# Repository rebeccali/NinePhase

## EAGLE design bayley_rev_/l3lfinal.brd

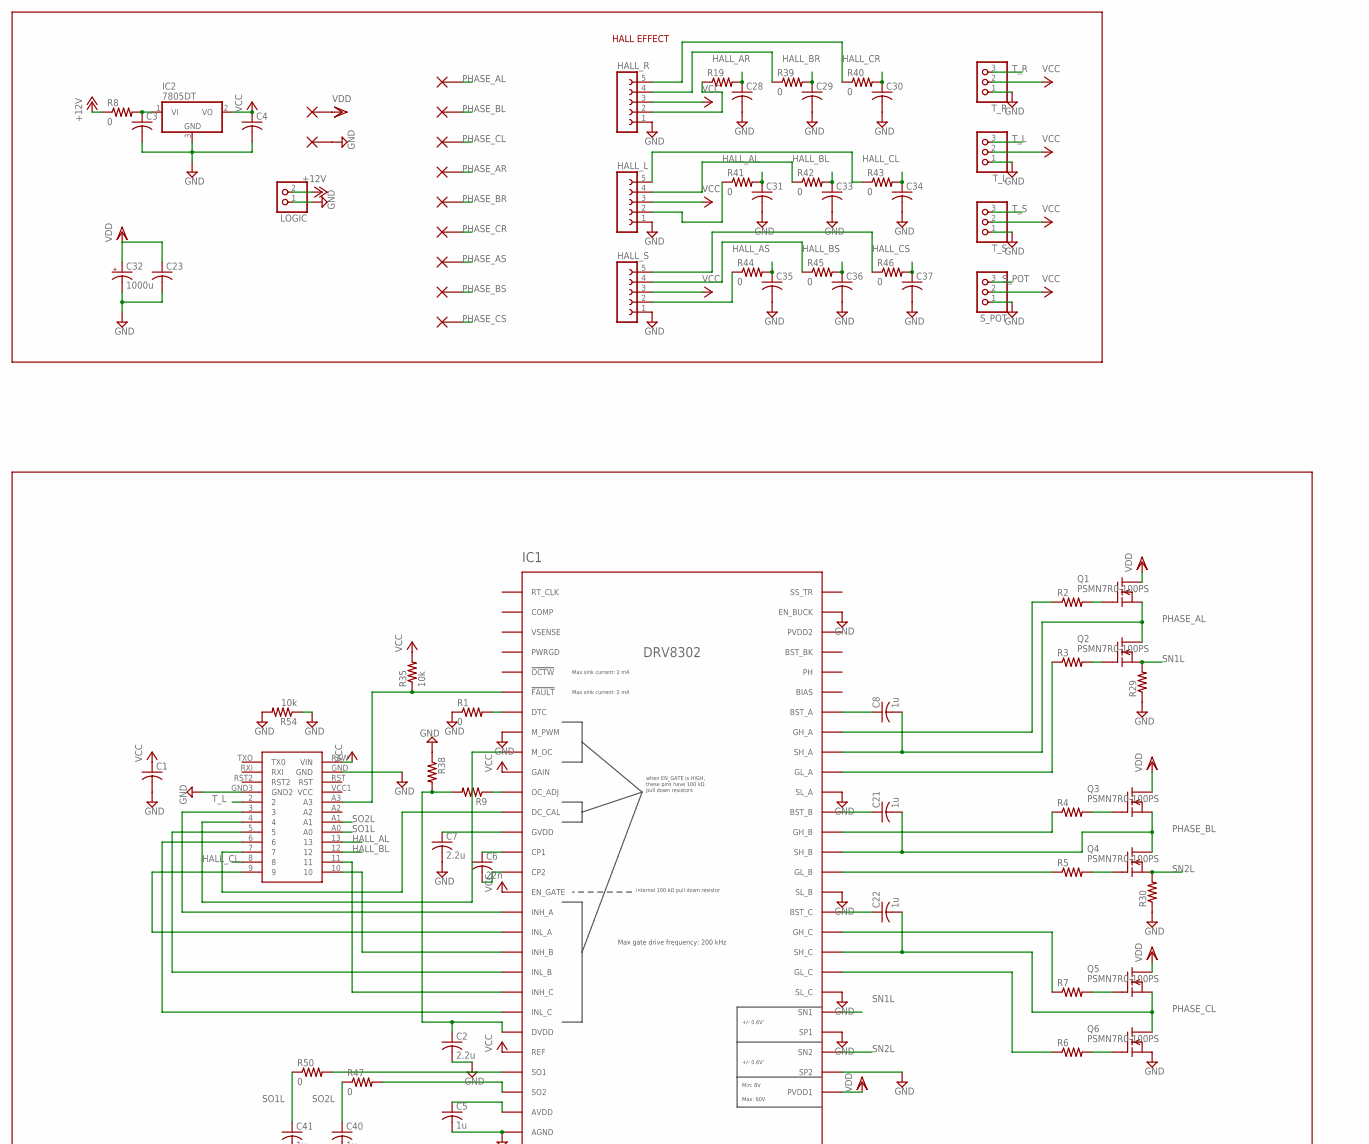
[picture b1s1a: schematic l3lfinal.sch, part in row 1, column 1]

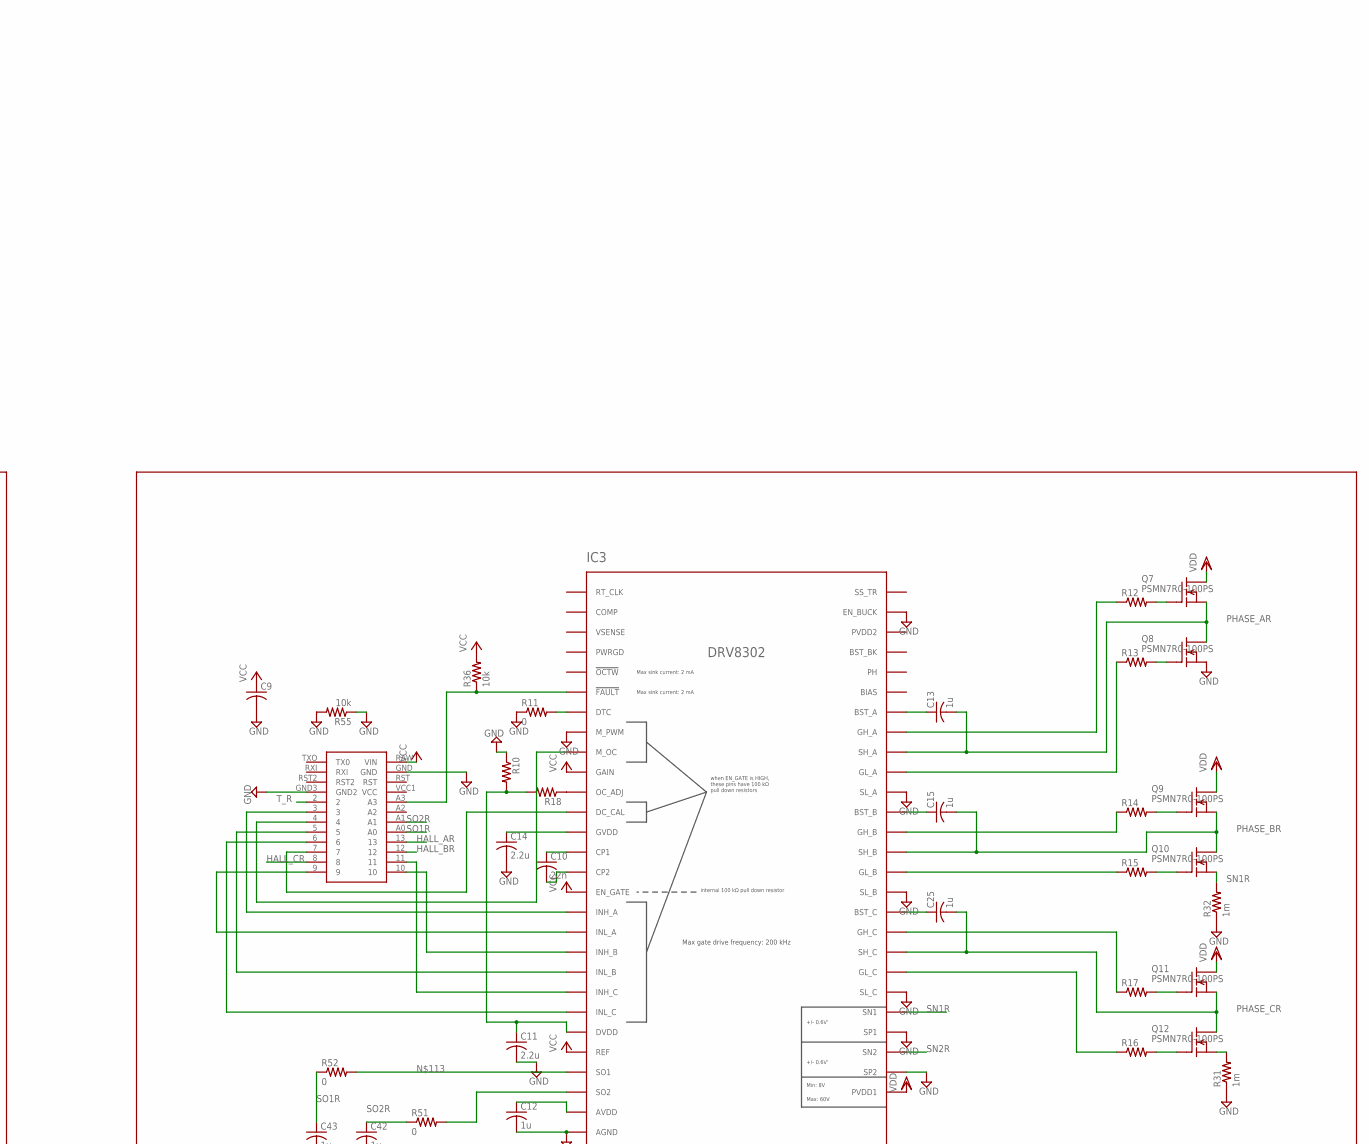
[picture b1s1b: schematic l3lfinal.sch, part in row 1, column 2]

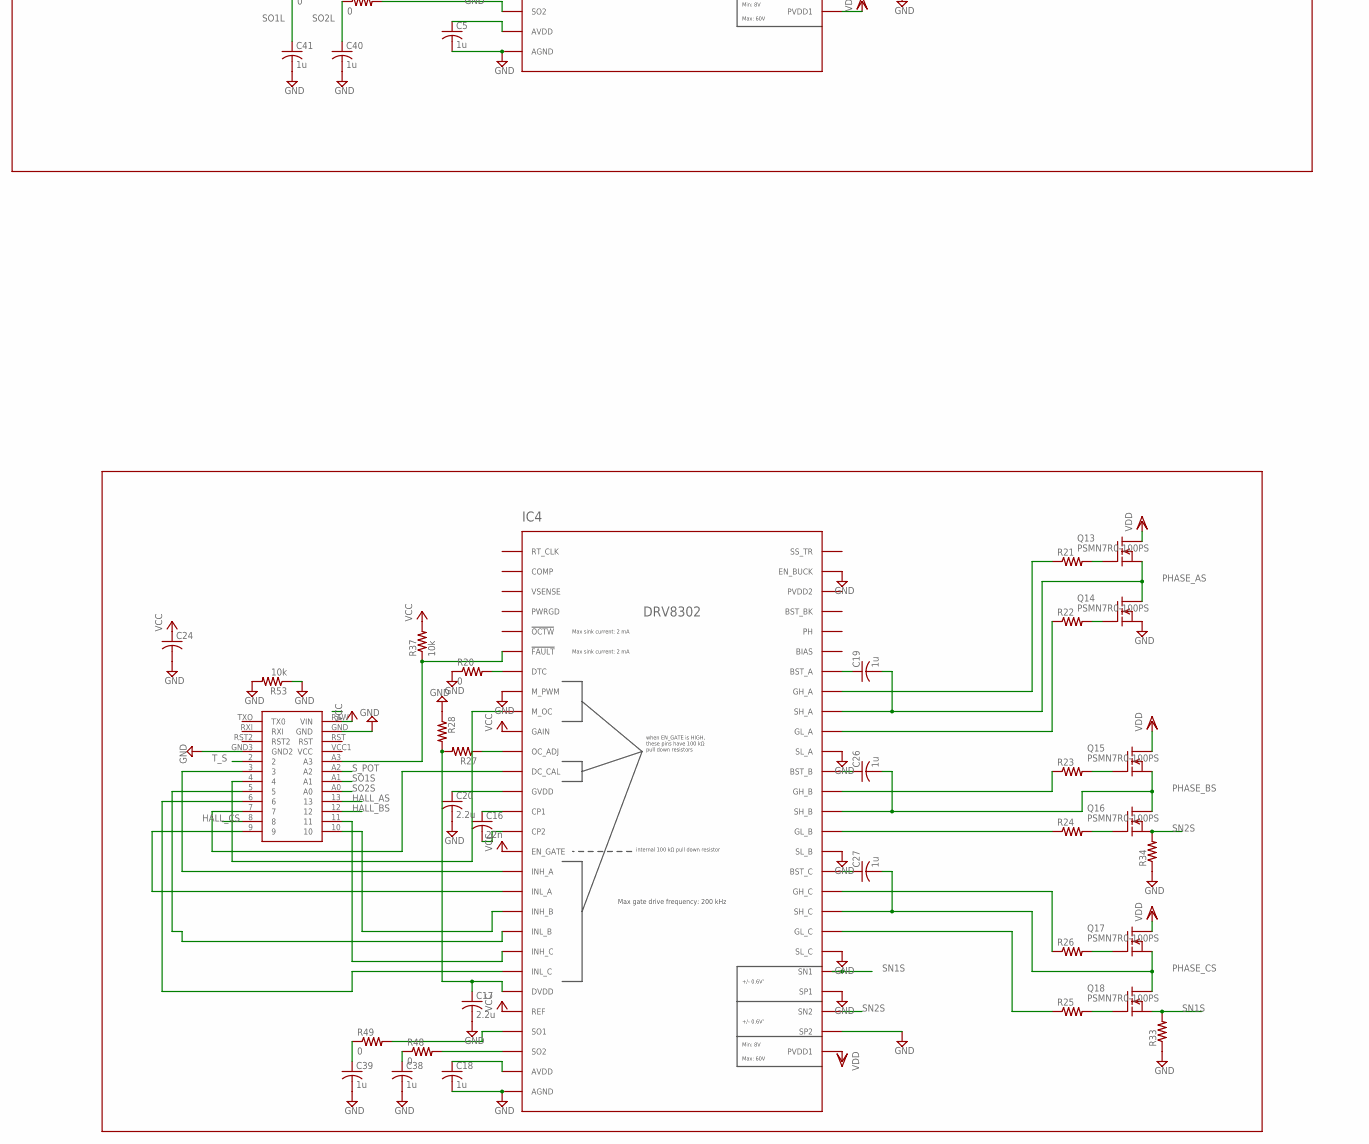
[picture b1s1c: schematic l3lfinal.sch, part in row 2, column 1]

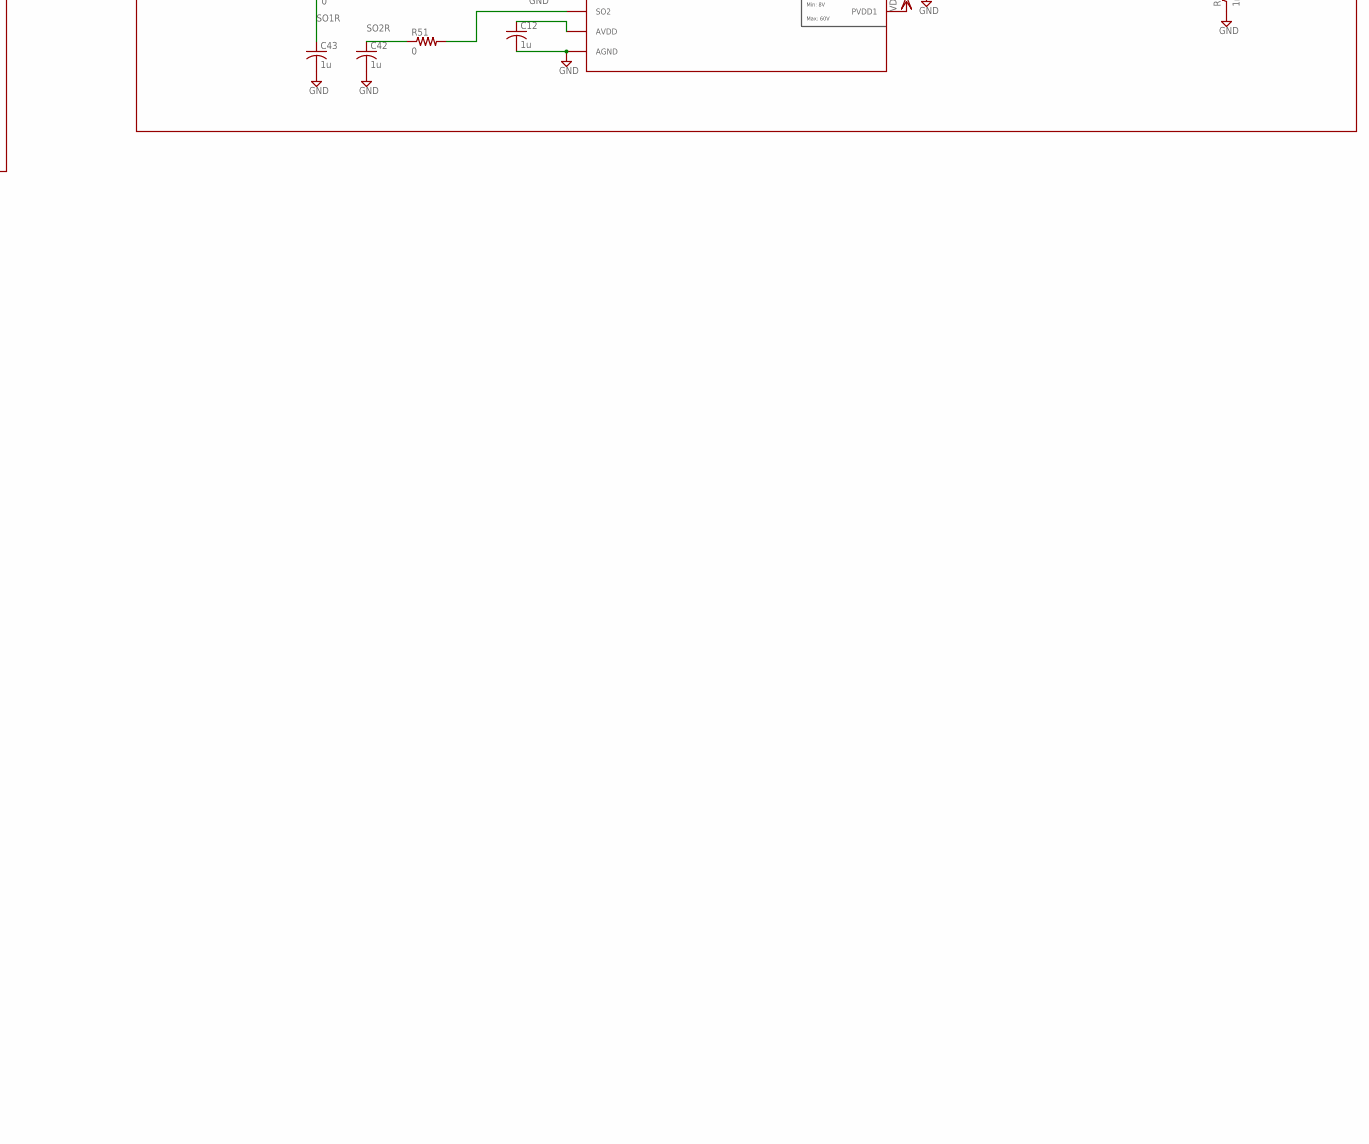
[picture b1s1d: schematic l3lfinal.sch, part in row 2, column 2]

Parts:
C1, C9, C24, C28, C29, C30, C31, C33, C34, C35, C36, C37: C-USC0805K; C0805K
C2, C7, C11, C14, C17, C20: 2.2u; C0805K
C3, C4, C23: C-USC1206K; C1206K
C5, C8, C12, C13, C15, C18, C19, C21, C22, C25, C26, C27, C38, C39, C40, C41, C42, C43: 1u; C0805K
C6, C10, C16: 22n; C0805K
C32: 1000u; E5-13
GND: 12AWG_PAD
HALL_L: FE05-1
HALL_R: FE05-1
HALL_S: FE05-1
IC1, IC3, IC4: DRV8302; TSSOP-56_3
IC2: 7805DT; TO252
LOGIC: PINHD-1X2; 1X02
PHASE_AL: 12AWG_PAD
PHASE_AR: 12AWG_PAD
PHASE_AS: 12AWG_PAD
PHASE_BL: 12AWG_PAD
PHASE_BR: 12AWG_PAD
PHASE_BS: 12AWG_PAD
PHASE_CL: 12AWG_PAD
PHASE_CR: 12AWG_PAD
PHASE_CS: 12AWG_PAD
Q1, Q2, Q3, Q4, Q5, Q6, Q7, Q8, Q9, Q10, Q11, Q12, Q13, Q14, Q15, Q16, Q17, Q18: PSMN7R0-100PS; TO220
R1, R8, R11, R20, R39, R40, R41, R42, R43, R44, R45, R46, R47, R48, R49, R50, R51, R52: 0; R0805
R2, R3, R4, R5, R6, R7, R9, R10, R12, R13, R14, R15, R16, R17, R18, R19, R21, R22, R23, R24, R25, R26, R27, R28, R38: R-US_R0805; R0805
R29, R30, R33, R34: R-US_R2512; R2512
R31, R32: 1m; R2512
R35, R36, R37, R53, R54, R55: 10k; R0805
S_POT: PINHD-1X3; 1X03
T_L: PINHD-1X3; 1X03
T_R: PINHD-1X3; 1X03
T_S: PINHD-1X3; 1X03
U$1, U$2, U$3: ARDUINOPROMINI
VDD: 12AWG_PAD

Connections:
+12V: LOGIC.2, R8.1
BST_BK: IC1.52 (BST_BK), IC3.52 (BST_BK), IC4.52 (BST_BK)
GND: C1.2, C2.2, C3.2, C4.2, C5.2, C7.2, C9.2, C11.2, C12.2, C14.2, C17.2, C18.2, C20.2, C23.2, C24.2, C28.2, C29.2, C30.2, C31.2, C32.-, C33.2, C34.2, C35.2, C36.2, C37.2, C38.2, C39.2, C40.2, C41.2, C42.2, C43.2, GND.P$1, HALL_L.1, HALL_R.1, HALL_S.1, IC1.8 (M_PWM), IC1.28 (AGND), IC1.30 (SP2), IC1.32 (SP1), IC1.34 (SL_C), IC1.39 (SL_B), IC1.44 (SL_A), IC1.55 (EN_BUCK), IC1.57 (AGND), IC1.58 (AGND), IC1.59 (AGND), IC2.3 (GND), IC3.8 (M_PWM), IC3.28 (AGND), IC3.30 (SP2), IC3.32 (SP1), IC3.34 (SL_C), IC3.39 (SL_B), IC3.44 (SL_A), IC3.55 (EN_BUCK), IC3.57 (AGND), IC3.58 (AGND), IC3.59 (AGND), IC4.8 (M_PWM), IC4.28 (AGND), IC4.30 (SP2), IC4.32 (SP1), IC4.34 (SL_C), IC4.39 (SL_B), IC4.44 (SL_A), IC4.55 (EN_BUCK), IC4.57 (AGND), IC4.58 (AGND), IC4.59 (AGND), LOGIC.1, Q6.2 (S), Q8.2 (S), Q14.2 (S), R1.1, R10.1, R11.1, R20.1, R28.1, R29.1, R30.1, R31.1, R32.1, R33.1, R34.1, R38.1, R53.1, R53.2, R54.1, R54.2, R55.1, R55.2, S_POT.1, T_L.1, T_R.1, T_S.1, U$1.GND, U$1.GND3 (GND2), U$2.GND, U$2.GND3 (GND2), U$3.GND, U$3.GND3 (GND2)
HALL_AL: C31.1, R41.2, U$1.13
HALL_AR: C28.1, R19.2, U$2.13
HALL_AS: C35.1, R44.2, U$3.13
HALL_BL: C33.1, R42.2, U$1.12
HALL_BR: C29.1, R39.2, U$2.12
HALL_BS: C36.1, R45.2, U$3.12
HALL_CL: C34.1, R43.2, U$1.8
HALL_CR: C30.1, R40.2, U$2.8
HALL_CS: C37.1, R46.2, U$3.8
unnamed: IC1.47 (GH_A), R2.1
unnamed: IC1.42 (GH_B), R4.1
unnamed: IC1.37 (GH_C), R7.1
unnamed: IC1.45 (GL_A), R3.1
unnamed: C13.1, IC3.48 (BST_A)
unnamed: C3.1, IC2.1 (VI), R8.2
unnamed: IC1.40 (GL_B), R5.1
unnamed: IC1.35 (GL_C), R6.1
unnamed: C15.1, IC3.43 (BST_B)
unnamed: IC1.17 (INH_A), U$1.3
unnamed: IC1.18 (INL_A), U$1.9
unnamed: IC1.20 (INL_B), U$1.5
unnamed: IC1.22 (INL_C), U$1.6
unnamed: IC1.19 (INH_B), U$1.10
unnamed: IC1.21 (INH_C), U$1.11
unnamed: IC1.7 (DTC), R1.2
unnamed: Q5.1 (G), R7.2
unnamed: Q6.1 (G), R6.2
unnamed: Q4.1 (G), R5.2
unnamed: Q3.1 (G), R4.2
unnamed: Q2.1 (G), R3.2
unnamed: Q1.1 (G), R2.2
unnamed: IC3.47 (GH_A), R12.1
unnamed: C5.1, IC1.27 (AVDD)
unnamed: IC1.9 (M_OC), U$1.4
unnamed: C2.1, IC1.23 (DVDD), R9.2, R38.2
unnamed: C6.1, IC1.14 (CP1)
unnamed: C6.2, IC1.15 (CP2)
unnamed: C8.1, IC1.48 (BST_A)
unnamed: C7.1, IC1.13 (GVDD)
unnamed: IC1.11 (OC_ADJ), R9.1
unnamed: IC3.42 (GH_B), R14.1
unnamed: IC3.37 (GH_C), R17.1
unnamed: IC3.45 (GL_A), R13.1
unnamed: IC3.40 (GL_B), R15.1
unnamed: IC3.35 (GL_C), R16.1
unnamed: IC3.17 (INH_A), U$2.3
unnamed: IC3.18 (INL_A), U$2.9
unnamed: IC3.20 (INL_B), U$2.5
unnamed: IC3.22 (INL_C), U$2.6
unnamed: IC4.20 (INL_B), U$3.5
unnamed: IC3.21 (INH_C), U$2.11
unnamed: IC3.7 (DTC), R11.2
unnamed: Q11.1 (G), R17.2
unnamed: Q12.1 (G), R16.2
unnamed: Q10.1 (G), R15.2
unnamed: Q9.1 (G), R14.2
unnamed: Q8.1 (G), R13.2
unnamed: Q7.1 (G), R12.2
unnamed: C12.1, IC3.27 (AVDD)
unnamed: IC3.9 (M_OC), U$2.4
unnamed: C11.1, IC3.23 (DVDD), R10.2, R18.2
unnamed: C10.1, IC3.14 (CP1)
unnamed: C10.2, IC3.15 (CP2)
unnamed: C25.1, IC3.38 (BST_C)
unnamed: C14.1, IC3.13 (GVDD)
unnamed: IC3.11 (OC_ADJ), R18.1
unnamed: C19.1, IC4.48 (BST_A)
unnamed: IC4.47 (GH_A), R21.1
unnamed: IC4.42 (GH_B), R23.1
unnamed: IC4.37 (GH_C), R26.1
unnamed: IC4.45 (GL_A), R22.1
unnamed: IC4.40 (GL_B), R24.1
unnamed: IC4.35 (GL_C), R25.1
unnamed: IC4.17 (INH_A), U$3.3
unnamed: IC4.18 (INL_A), U$3.9
unnamed: HALL_L.2, R41.1
unnamed: IC4.22 (INL_C), U$3.6
unnamed: IC4.19 (INH_B), U$3.10
unnamed: IC4.21 (INH_C), U$3.11
unnamed: IC4.7 (DTC), R20.2
unnamed: Q17.1 (G), R26.2
unnamed: Q18.1 (G), R25.2
unnamed: Q16.1 (G), R24.2
unnamed: Q15.1 (G), R23.2
unnamed: Q14.1 (G), R22.2
unnamed: Q13.1 (G), R21.2
unnamed: C18.1, IC4.27 (AVDD)
unnamed: IC4.9 (M_OC), U$3.4
unnamed: C17.1, IC4.23 (DVDD), R27.2, R28.2
unnamed: C16.1, IC4.14 (CP1)
unnamed: C16.2, IC4.15 (CP2)
unnamed: C26.1, IC4.43 (BST_B)
unnamed: C20.1, IC4.13 (GVDD)
unnamed: IC4.11 (OC_ADJ), R27.1
unnamed: C27.1, IC4.38 (BST_C)
unnamed: IC3.12 (DC_CAL), U$2.7
unnamed: C21.1, IC1.43 (BST_B)
unnamed: C22.1, IC1.38 (BST_C)
unnamed: IC1.12 (DC_CAL), U$1.7
unnamed: IC1.6 (!FAULT!), R35.1, U$1.A3
unnamed: IC4.6 (!FAULT!), R37.1, U$3.A3
unnamed: IC3.6 (!FAULT!), R36.1, U$2.A3
unnamed: IC3.19 (INH_B), U$2.10
unnamed: HALL_L.4, R42.1
unnamed: HALL_L.5, R43.1
unnamed: HALL_R.2, R19.1
unnamed: HALL_R.4, R39.1
unnamed: HALL_R.5, R40.1
unnamed: HALL_S.2, R44.1
unnamed: HALL_S.4, R45.1
unnamed: HALL_S.5, R46.1
unnamed: IC4.12 (DC_CAL), U$3.7
unnamed: IC4.26 (SO2), R48.2
unnamed: IC4.25 (SO1), R49.2
unnamed: IC1.26 (SO2), R47.2
unnamed: IC1.25 (SO1), R50.2
unnamed: IC3.26 (SO2), R51.2
unnamed: IC3.25 (SO1), R52.2
PHASE_AL: C8.2, IC1.46 (SH_A), PHASE_AL.P$1, Q1.2 (S), Q2.3 (D)
PHASE_AR: C13.2, IC3.46 (SH_A), PHASE_AR.P$1, Q7.2 (S), Q8.3 (D)
PHASE_AS: C19.2, IC4.46 (SH_A), PHASE_AS.P$1, Q13.2 (S), Q14.3 (D)
PHASE_BL: C21.2, IC1.41 (SH_B), PHASE_BL.P$1, Q3.2 (S), Q4.3 (D)
PHASE_BR: C15.2, IC3.41 (SH_B), PHASE_BR.P$1, Q9.2 (S), Q10.3 (D)
PHASE_BS: C26.2, IC4.41 (SH_B), PHASE_BS.P$1, Q15.2 (S), Q16.3 (D)
PHASE_CL: C22.2, IC1.36 (SH_C), PHASE_CL.P$1, Q5.2 (S), Q6.3 (D)
PHASE_CR: C25.2, IC3.36 (SH_C), PHASE_CR.P$1, Q11.2 (S), Q12.3 (D)
PHASE_CS: C27.2, IC4.36 (SH_C), PHASE_CS.P$1, Q17.2 (S), Q18.3 (D)
SN1L: IC1.33 (SN1), Q2.2 (S), R29.2
SN1R: IC3.33 (SN1), Q10.2 (S), R32.2
SN1S: IC4.33 (SN1), Q18.2 (S), R33.2
SN2L: IC1.31 (SN2), Q4.2 (S), R30.2
SN2R: IC3.31 (SN2), Q12.2 (S), R31.2
SN2S: IC4.31 (SN2), Q16.2 (S), R34.2
SO1L: C41.1, R50.1, U$1.A0
SO1R: C43.1, R52.1, U$2.A0
SO1S: C39.1, R49.1, U$3.A1
SO2L: C40.1, R47.1, U$1.A1
SO2R: C42.1, R51.1, U$2.A1
SO2S: C38.1, R48.1, U$3.A0
S_POT: S_POT.3, U$3.A2
T_L: T_L.3, U$1.2
T_R: T_R.3, U$2.2
T_S: T_S.3, U$3.2
VCC: C1.1, C4.1, C9.1, C24.1, HALL_L.3, HALL_R.3, HALL_S.3, IC1.10 (GAIN), IC1.16 (EN_GATE), IC1.24 (REF), IC2.2 (VO), IC3.10 (GAIN), IC3.16 (EN_GATE), IC3.24 (REF), IC4.10 (GAIN), IC4.16 (EN_GATE), IC4.24 (REF), R35.2, R36.2, R37.2, S_POT.2, T_L.2, T_R.2, T_S.2, U$1.RAW (VIN), U$2.RAW (VIN), U$3.RAW (VIN)
VDD: C23.1, C32.+, IC1.29 (PVDD1), IC3.29 (PVDD1), IC4.29 (PVDD1), Q1.3 (D), Q3.3 (D), Q5.3 (D), Q7.3 (D), Q9.3 (D), Q11.3 (D), Q13.3 (D), Q15.3 (D), Q17.3 (D), VDD.P$1

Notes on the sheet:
HALL EFFECT

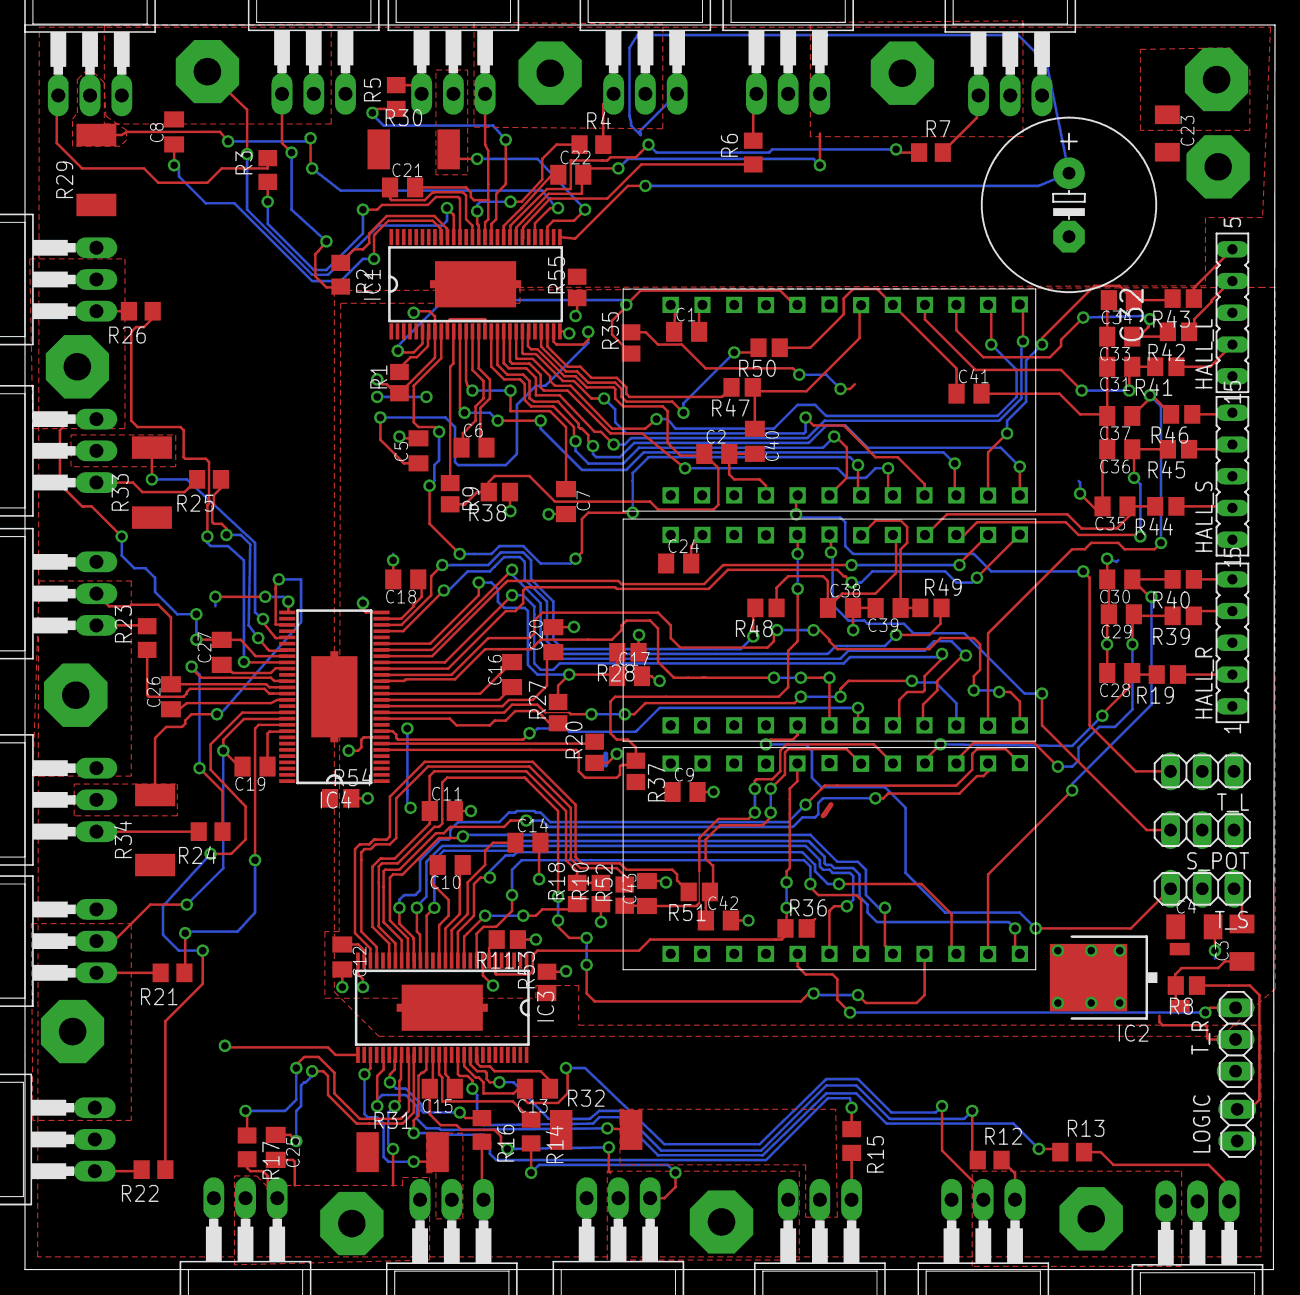
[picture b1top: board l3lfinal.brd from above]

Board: 2 copper layers, 100.1 x 99.6 mm, 142 parts (0 on the bottom side), 148 nets.

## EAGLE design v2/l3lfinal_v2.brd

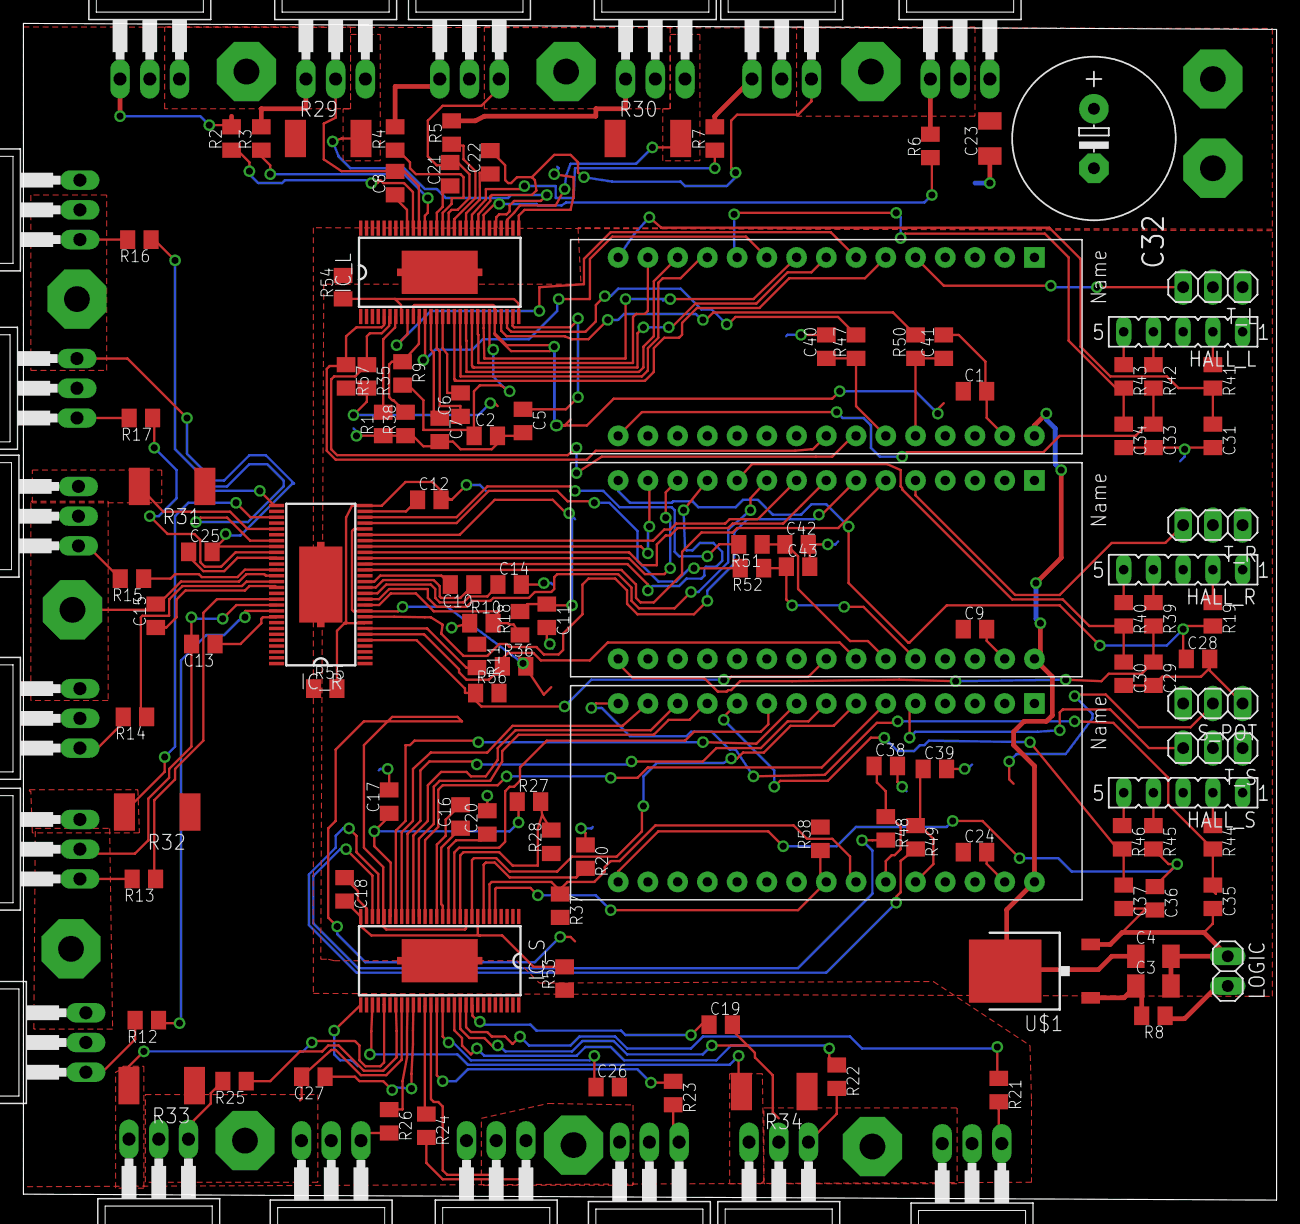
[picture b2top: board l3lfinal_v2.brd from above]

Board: 2 copper layers, 107.0 x 100.5 mm, 145 parts (0 on the bottom side), 151 nets.

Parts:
C1, C9, C24: .1uF; C0805K
C2, C7, C11, C14, C17, C20: 2.2u; C0805K
C3, C23: 22uF; C1206K
C4: 1uF 50V; C1206K
C5, C8, C12, C13, C15, C18, C19, C21, C22, C25, C26, C27, C38, C39, C40, C41, C42, C43: 1u; C0805K
C6, C10, C16: 22n; C0805K
C28, C29, C30, C31, C33, C34, C35, C36, C37: C0805K
C32: 1000u; E5-13
GND: 12AWG_PAD
HALL_L: FE05-1
HALL_R: FE05-1
HALL_S: FE05-1
IC_L: DRV8302; TSSOP-56_3
IC_R: DRV8302; TSSOP-56_3
IC_S: DRV8302; TSSOP-56_3
LOGIC: 1X02
NANO_L: ARDUINONANO; PDIP-32
NANO_R: ARDUINONANO; PDIP-32
NANO_S: ARDUINONANO; PDIP-32
PHASE_AL: 12AWG_PAD
PHASE_AR: 12AWG_PAD
PHASE_AS: 12AWG_PAD
PHASE_BL: 12AWG_PAD
PHASE_BR: 12AWG_PAD
PHASE_BS: 12AWG_PAD
PHASE_CL: 12AWG_PAD
PHASE_CR: 12AWG_PAD
PHASE_CS: 12AWG_PAD
Q1, Q2, Q3, Q4, Q5, Q6, Q7, Q8, Q9, Q10, Q11, Q12, Q13, Q14, Q15, Q16, Q17, Q18: PSMN7R0-100PS; TO220
R1, R8, R11, R20, R39, R40, R41, R42, R43, R44, R45, R46, R47, R48, R49, R50, R51, R52, R53, R54, R55: 0; C0805K
R2, R3, R4, R5, R6, R7, R12, R13, R14, R15, R16, R17, R21, R22, R23, R24, R25, R26: 10; C0805K
R9, R18, R27: 5k; C0805K
R10, R28, R35, R36, R37, R38, R56, R57, R58: 10k; C0805K
R19: C0805K
R29, R30, R31, R32, R33, R34: 1m; R2512
S_POT: 1X03
T_L: 1X03
T_R: 1X03
T_S: 1X03
U$1: 7809; TO252
VDD: 12AWG_PAD

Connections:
+12V: LOGIC.2, R8.1
BST_BK: IC_L.52, IC_R.52, IC_S.52
DC_CAL_L: IC_L.12, NANO_L.D7
DC_CAL_R: IC_R.12, NANO_R.D7
DC_CAL_S: IC_S.12, NANO_S.D7
DVDDL: C2.1, IC_L.23, R9.2
DVDDR: C11.1, IC_R.23, R18.2
DVDDS: C17.1, IC_S.23, R27.1
FAULT_L: IC_L.6, NANO_L.A2, R35.1
FAULT_R: IC_R.6, NANO_R.A2, R36.1
FAULT_S: IC_S.6, NANO_S.A2, R37.1
GND: C1.2, C2.2, C3.2, C4.2, C5.2, C7.2, C9.2, C11.2, C12.2, C14.2, C17.2, C18.2, C20.2, C23.2, C24.2, C28.2, C29.2, C30.2, C31.2, C32.-, C33.2, C34.2, C35.2, C36.2, C37.2, C38.2, C39.2, C40.2, C41.2, C42.2, C43.2, GND.P$1, HALL_L.1, HALL_R.1, HALL_S.1, IC_L.8, IC_L.28, IC_L.30, IC_L.32, IC_L.34, IC_L.39, IC_L.44, IC_L.55, IC_L.57, IC_L.58, IC_L.59, IC_R.8, IC_R.28, IC_R.30, IC_R.32, IC_R.34, IC_R.39, IC_R.44, IC_R.55, IC_R.57, IC_R.58, IC_R.59, IC_S.8, IC_S.28, IC_S.30, IC_S.32, IC_S.34, IC_S.39, IC_S.44, IC_S.55, IC_S.57, IC_S.58, IC_S.59, LOGIC.1, NANO_L.GND, NANO_L.GND1, NANO_R.GND, NANO_R.GND1, NANO_S.GND, NANO_S.GND1, Q6.3, Q12.3, Q16.3, R1.1, R10.1, R11.1, R20.1, R28.1, R29.1, R30.1, R31.1, R32.1, R33.1, R34.1, R38.1, R53.1, R53.2, R54.1, R54.2, R55.1, R55.2, S_POT.1, T_L.1, T_R.1, T_S.1, U$1.2
HAL: IC_L.17, NANO_L.D3
HALL_AL: C31.1, NANO_L.D12, R41.2
HALL_AR: C28.1, NANO_R.D12, R19.2
HALL_AS: C35.1, NANO_S.D12, R44.2
HALL_BL: C33.1, NANO_L.D13, R42.2
HALL_BR: C29.1, NANO_R.D13, R39.2
HALL_BS: C36.1, NANO_S.D13, R45.2
HALL_CL: C34.1, NANO_L.D8, R43.2
HALL_CR: C30.1, NANO_R.D8, R40.2
HALL_CS: C37.1, NANO_S.D8, R46.2
HAR: IC_R.17, NANO_R.D3
HAS: IC_S.17, NANO_S.D3
HBL: IC_L.19, NANO_L.D10
HBR: IC_R.19, NANO_R.D10
HBS: IC_S.19, NANO_S.D10
HCL: IC_L.21, NANO_L.D11
HCR: IC_R.21, NANO_R.D11
HCS: IC_S.21, NANO_S.D11
LAL: IC_L.18, NANO_L.D9
LAR: IC_R.18, NANO_R.D9
LAS: IC_S.18, NANO_S.D9
LBL: IC_L.20, NANO_L.D5
LBR: IC_R.20, NANO_R.D5
LBS: IC_S.20, NANO_S.D5
LCL: IC_L.22, NANO_L.D6
LCR: IC_R.22, NANO_R.D6
LCS: IC_S.22, NANO_S.D6
M_OC_L: IC_L.9, NANO_L.D4
M_OC_R: IC_R.9, NANO_R.D4
M_OC_S: IC_S.9, NANO_S.D4
unnamed: IC_L.47, R2.1
unnamed: IC_L.42, R4.1
unnamed: IC_L.37, R7.1
unnamed: IC_L.45, R3.1
unnamed: C13.1, IC_R.48
unnamed: C3.1, R8.2, U$1.1
unnamed: IC_L.40, R5.1
unnamed: IC_L.35, R6.1
unnamed: C15.1, IC_R.43
unnamed: IC_L.7, R1.2
unnamed: Q5.1, R7.2
unnamed: Q6.1, R6.2
unnamed: Q4.1, R5.2
unnamed: Q3.1, R4.2
unnamed: Q2.1, R3.2
unnamed: Q1.1, R2.2
unnamed: IC_R.47, R12.1
unnamed: C5.1, IC_L.27
unnamed: C6.1, IC_L.14
unnamed: C6.2, IC_L.15
unnamed: C8.1, IC_L.48
unnamed: C7.1, IC_L.13
unnamed: IC_L.11, R9.1, R38.2
unnamed: IC_R.42, R14.1
unnamed: IC_R.37, R17.1
unnamed: IC_R.45, R13.1
unnamed: IC_R.40, R15.1
unnamed: IC_R.35, R16.1
unnamed: IC_R.7, R11.2
unnamed: Q11.1, R17.2
unnamed: Q12.1, R16.2
unnamed: Q10.1, R15.2
unnamed: Q9.1, R14.2
unnamed: Q8.1, R13.2
unnamed: Q7.1, R12.2
unnamed: C12.1, IC_R.27
unnamed: C10.1, IC_R.14
unnamed: C10.2, IC_R.15
unnamed: C25.1, IC_R.38
unnamed: C14.1, IC_R.13
unnamed: IC_R.11, R10.2, R18.1
unnamed: C19.1, IC_S.48
unnamed: IC_S.47, R21.1
unnamed: IC_S.42, R23.1
unnamed: IC_S.37, R26.1
unnamed: IC_S.45, R22.1
unnamed: IC_S.40, R24.1
unnamed: IC_S.35, R25.1
unnamed: HALL_L.2, R41.1
unnamed: IC_S.7, R20.2
unnamed: Q17.1, R26.2
unnamed: Q18.1, R25.2
unnamed: Q16.1, R24.2
unnamed: Q15.1, R23.2
unnamed: Q14.1, R22.2
unnamed: Q13.1, R21.2
unnamed: C18.1, IC_S.27
unnamed: C16.1, IC_S.14
unnamed: C16.2, IC_S.15
unnamed: C26.1, IC_S.43
unnamed: C20.1, IC_S.13
unnamed: C27.1, IC_S.38
unnamed: C21.1, IC_L.43
unnamed: C22.1, IC_L.38
unnamed: IC_S.11, R27.2, R28.2
unnamed: HALL_L.4, R42.1
unnamed: HALL_L.5, R43.1
unnamed: HALL_R.2, R19.1
unnamed: HALL_R.4, R39.1
unnamed: HALL_R.5, R40.1
unnamed: HALL_S.2, R44.1
unnamed: HALL_S.4, R45.1
unnamed: HALL_S.5, R46.1
unnamed: IC_S.26, R48.2
unnamed: IC_S.25, R49.2
unnamed: IC_L.26, R47.2
unnamed: IC_L.25, R50.2
unnamed: IC_R.26, R51.2
unnamed: IC_R.25, R52.2
OCTW_L: IC_L.5, NANO_L.A3, R57.1
OCTW_R: IC_R.5, NANO_R.A3, R56.1
OCTW_S: IC_S.5, NANO_S.A3, R58.1
PHASE_AL: C8.2, IC_L.46, PHASE_AL.P$1, Q1.3, Q2.2
PHASE_AR: C13.2, IC_R.46, PHASE_AR.P$1, Q7.3, Q8.2
PHASE_AS: C19.2, IC_S.46, PHASE_AS.P$1, Q13.3, Q14.2
PHASE_BL: C21.2, IC_L.41, PHASE_BL.P$1, Q3.3, Q4.2
PHASE_BR: C15.2, IC_R.41, PHASE_BR.P$1, Q9.3, Q10.2
PHASE_BS: C26.2, IC_S.41, PHASE_BS.P$1, Q15.3, Q16.2
PHASE_CL: C22.2, IC_L.36, PHASE_CL.P$1, Q5.3, Q6.2
PHASE_CR: C25.2, IC_R.36, PHASE_CR.P$1, Q11.3, Q12.2
PHASE_CS: C27.2, IC_S.36, PHASE_CS.P$1, Q17.3, Q18.2
SN1L: IC_L.33, Q2.3, R29.2
SN1R: IC_R.33, Q10.3, R31.2
SN1S: IC_S.33, Q18.3, R33.2
SN2L: IC_L.31, Q4.3, R30.2
SN2R: IC_R.31, Q8.3, R32.2
SN2S: IC_S.31, Q14.3, R34.2
SO1L: C41.1, NANO_L.A0, R50.1
SO1R: C43.1, NANO_R.A0, R52.1
SO1S: C39.1, NANO_S.A0, R49.1
SO2L: C40.1, NANO_L.A1, R47.1
SO2R: C42.1, NANO_R.A1, R51.1
SO2S: C38.1, NANO_S.A1, R48.1
T_L: NANO_L.D2, T_L.3
T_R: NANO_R.D2, T_R.3
T_S: NANO_S.D2, T_S.3
VCC: C1.1, C9.1, C24.1, HALL_L.3, HALL_R.3, HALL_S.3, IC_L.10, IC_L.16, IC_L.24, IC_R.10, IC_R.16, IC_R.24, IC_S.10, IC_S.16, IC_S.24, NANO_L.+5V, NANO_R.+5V, NANO_S.+5V, R35.2, R36.2, R37.2, R56.2, R57.2, R58.2, S_POT.2, T_L.2, T_R.2, T_S.2
VDD: C23.1, C32.+, IC_L.29, IC_R.29, IC_S.29, Q1.2, Q3.2, Q5.2, Q7.2, Q9.2, Q11.2, Q13.2, Q15.2, Q17.2, VDD.P$1
VEE: C4.1, NANO_L.VIN, NANO_R.VIN, NANO_S.VIN, U$1.3

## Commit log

2015-12-11 :space_invader: Added .gitattributes & .gitignore files
2015-12-11 Added all parts
